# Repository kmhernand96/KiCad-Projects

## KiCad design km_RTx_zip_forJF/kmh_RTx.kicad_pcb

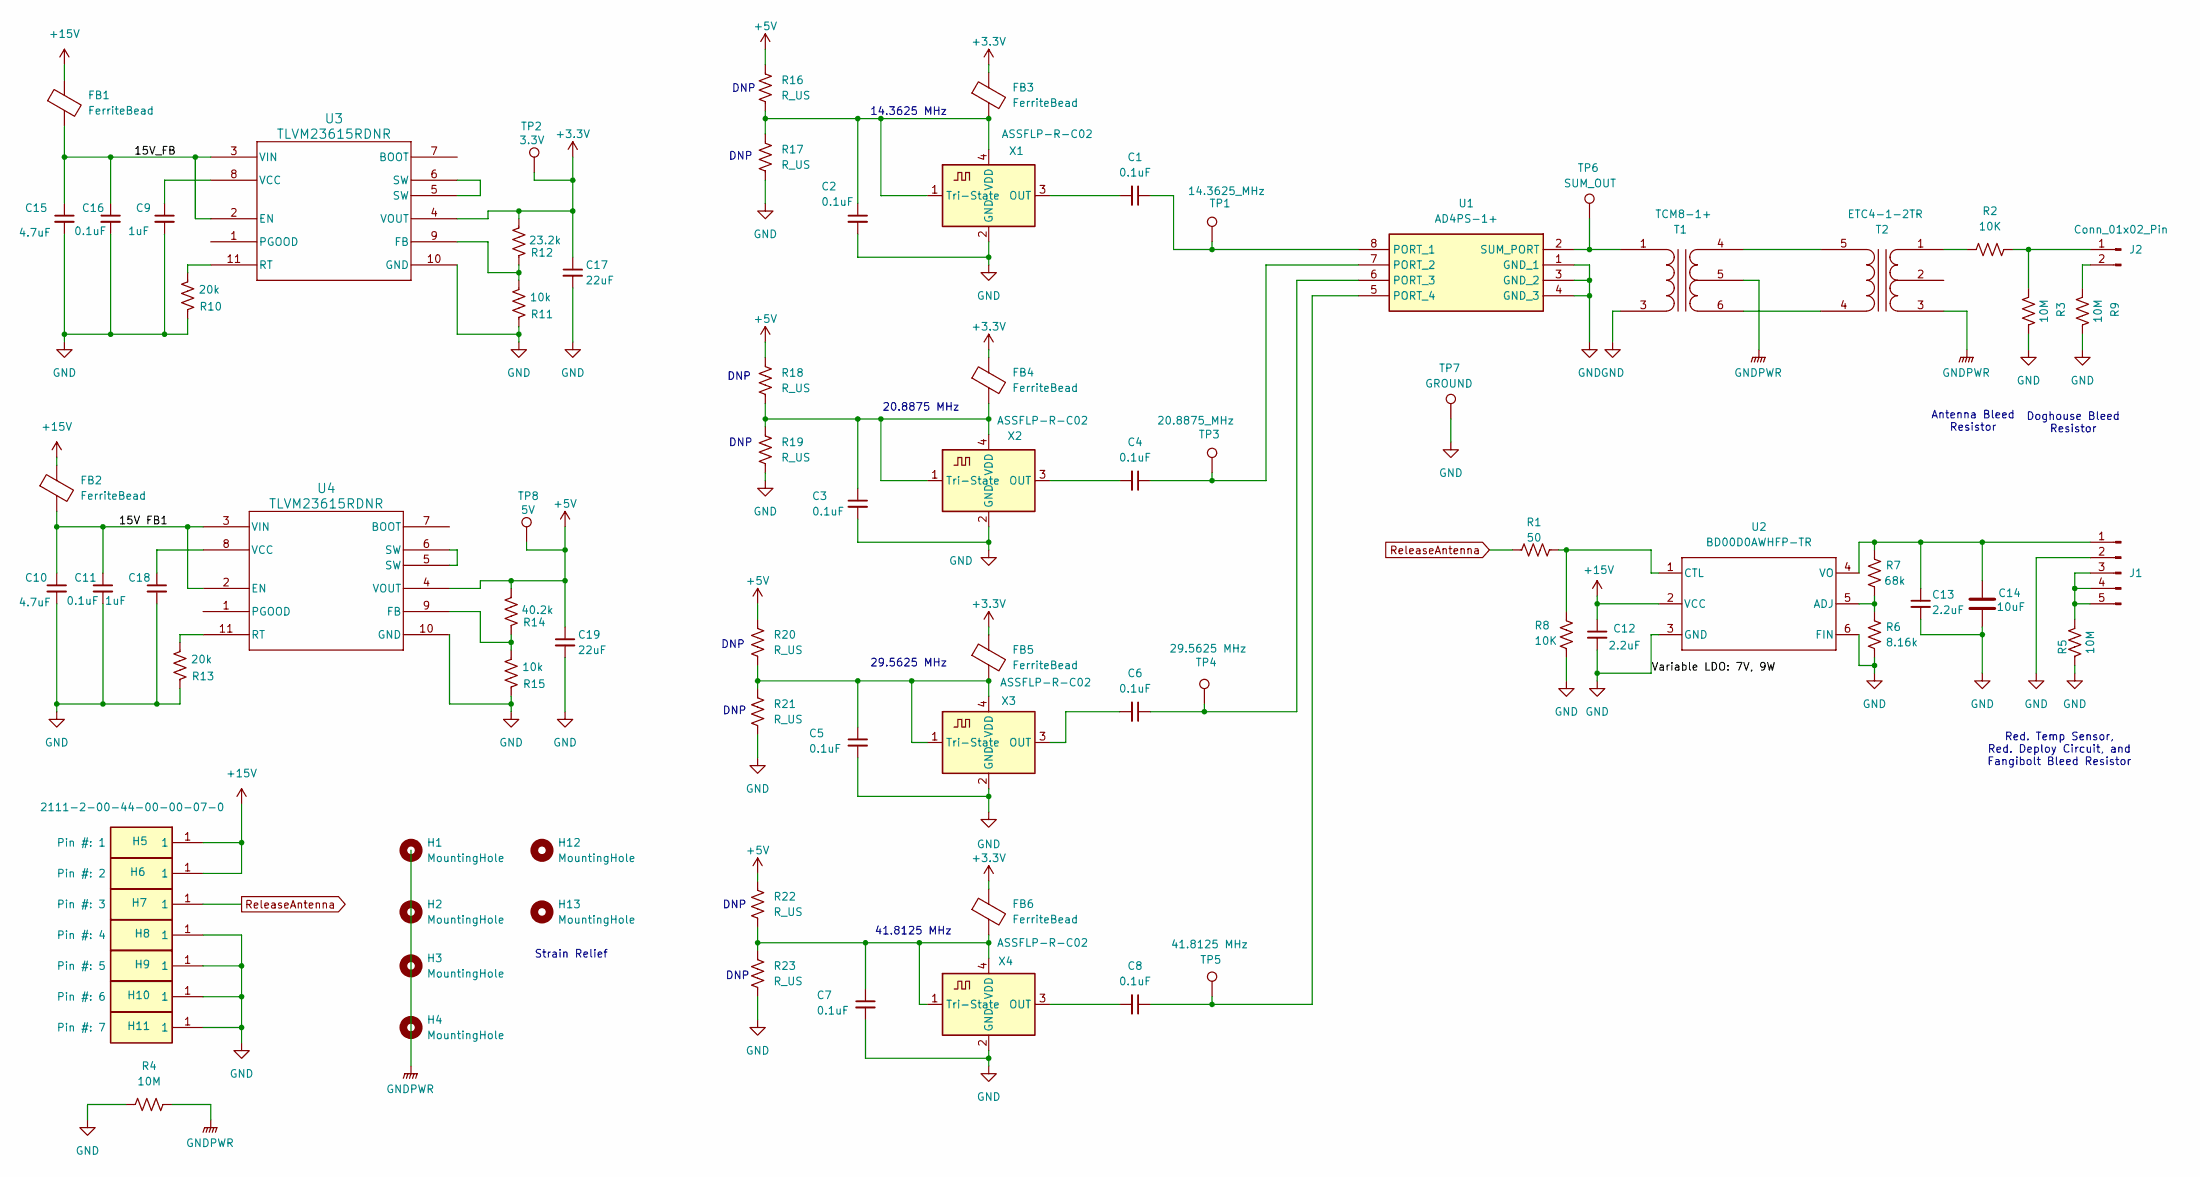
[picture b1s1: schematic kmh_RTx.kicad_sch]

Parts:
C1, C2, C3, C4, C5, C6, C7, C8, C11, C16: 0.1uF; C_0603_1608Metric
C9, C18: 1uF; C_0603_1608Metric
C10, C15: 4.7uF; C_1206_3216Metric
C12, C13: 2.2uF; C_1206_3216Metric
C14: 10uF; C_0805_2012Metric
C17, C19: 22uF; D_0805_2012Metric
FB1, FB2, FB3, FB4, FB5, FB6: FerriteBead; L_0805_2012Metric
H1, H2, H3, H4, H12, H13: MountingHole; MountingHole_2.5mm
H5, H6, H7, H8, H9, H10, H11: 2111-2-00-44-00-00-07-0; 2111200440000070; Mouser Part Number 575-2111200440000
J1: Conn_01x06_Pin; 22272051
J2: Conn_01x02_Pin; 22232021
R1: 50; R_0603_1608Metric
R2, R8: 10K; R_0603_1608Metric
R3, R4, R5, R9: 10M; R_0603_1608Metric
R6: 8.16k; R_0603_1608Metric
R7: 68k; R_0603_1608Metric
R10, R13: 20k; R_0603_1608Metric
R11, R15: 10k; R_0603_1608Metric
R12: 23.2k; R_0603_1608Metric
R14: 40.2k; R_0603_1608Metric
R16, R17, R18, R19, R20, R21, R22, R23: R_US; R_0603_1608Metric
T1: TCM8-1+; TCM81; Manufacturer_Part_Number TCM8-1+
T2: ETC4-1-2TR; ETC4_1_2TR; Manufacturer_Part_Number ETC4-1-2TR; Mouser Part Number 937-ETC4-1-2TR
TP1: 14.3625_MHz; 5000
TP2: 3.3V; Pin_D0.7mm_L6.5mm_W1.8mm_FlatFork
TP3: 20.8875_MHz; 5000
TP4: 29.5625 MHz; 5000
TP5: 41.8125 MHz; 5000
TP6: SUM_OUT; 5000
TP7: GROUND; 5000
TP8: 5V; Pin_D0.7mm_L6.5mm_W1.8mm_FlatFork
U1: AD4PS-1+; AD4PS1; Mouser Part Number 139-AD4PS-1
U2: BD00D0AWHFP-TR; HRP5_ROM; Manufacturer_Part_Number BD80FD0WHFP-TR; Mouser Part Number 755-BD80FD0WHFP-TR
U3, U4: TLVM23615RDNR; TLVM23615
X1, X2, X3, X4: ASSFLP-R-C02; Crystal_SMD_Abracon_ABM3B-4Pin_5.0x3.2mm

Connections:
+3.3V: C17.1, FB3.1, FB4.1, FB5.1, FB6.1, R12.2, TP2.1, U3.4 (VOUT)
+5V: C19.1, R14.2, R16.1, R18.1, R20.1, R22.1, TP8.1, U4.4 (VOUT)
+15V: C12.1, FB1.1, FB2.1, H5.1, H6.1, U2.2 (VCC)
/15V FB1: C10.1, C11.1, FB2.2, U4.2 (EN), U4.3 (VIN)
/15V_FB: C15.1, C16.1, FB1.2, U3.2 (EN), U3.3 (VIN)
GND: C2.2, C3.2, C5.2, C7.2, C9.2, C10.2, C11.2, C12.2, C13.2, C14.2, C15.2, C16.2, C17.2, C18.2, C19.2, H8.1, H9.1, H10.1, H11.1, J1.2, R3.1, R4.1, R5.1, R6.2, R8.2, R9.1, R10.1, R11.1, R13.1, R15.1, R17.2, R19.2, R21.2, R23.2, T1.3 (AB), TP7.1, U1.1 (GND_1), U1.3 (GND_2), U1.4 (GND_3), U2.3 (GND), U2.6 (FIN), U3.10 (GND), U4.10 (GND), X1.2 (GND), X2.2 (GND), X3.2 (GND), X4.2 (GND)
GNDPWR: R4.2, T1.5 (SC), T2.3 (SA)
unnamed: C13.1, C14.1, J1.1, R7.1, U2.4 (VO)
unnamed: J1.3, J1.4, J1.5, R5.2
unnamed: J2.1, R2.2, R3.2
unnamed: J2.2, R9.2
unnamed: T1.1 (AA), TP6.1, U1.2 (SUM_PORT)
unnamed: T1.6 (SA), T2.4 (AB)
unnamed: T1.4 (SB), T2.5 (AA)
unnamed: R2.1, T2.1 (SB)
unnamed: C1.1, TP1.1, U1.8 (PORT_1)
unnamed: C4.1, TP3.1, U1.7 (PORT_2)
unnamed: C6.1, TP4.1, U1.6 (PORT_3)
unnamed: C8.1, TP5.1, U1.5 (PORT_4)
unnamed: R6.1, R7.2, U2.5 (ADJ)
unnamed: R1.2, R8.1, U2.1 (CTL)
unnamed: R11.2, R12.1, U3.9 (FB)
unnamed: R10.2, U3.11 (RT)
unnamed: U3.5 (SW), U3.6 (SW)
unnamed: C9.1, U3.8 (VCC)
unnamed: R14.1, R15.2, U4.9 (FB)
unnamed: R13.2, U4.11 (RT)
unnamed: U4.5 (SW), U4.6 (SW)
unnamed: C18.1, U4.8 (VCC)
unnamed: C1.2, X1.3 (OUT)
unnamed: C2.1, FB3.2, R16.2, R17.1, X1.1 (Tri-State), X1.4 (VDD)
unnamed: C4.2, X2.3 (OUT)
unnamed: C3.1, FB4.2, R18.2, R19.1, X2.1 (Tri-State), X2.4 (VDD)
unnamed: C6.2, X3.3 (OUT)
unnamed: C5.1, FB5.2, R20.2, R21.1, X3.1 (Tri-State), X3.4 (VDD)
unnamed: C8.2, X4.3 (OUT)
unnamed: C7.1, FB6.2, R22.2, R23.1, X4.1 (Tri-State), X4.4 (VDD)
ReleaseAntenna: H7.1, R1.1

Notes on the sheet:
DNP
Doghouse Bleed Resistor
14.3625 MHz
20.8875 MHz
29.5625 MHz
Antenna Bleed Resistor
41.8125 MHz
Strain Relief
Red. Temp Sensor, Red. Deploy Circuit, and Fangibolt Bleed Resistor

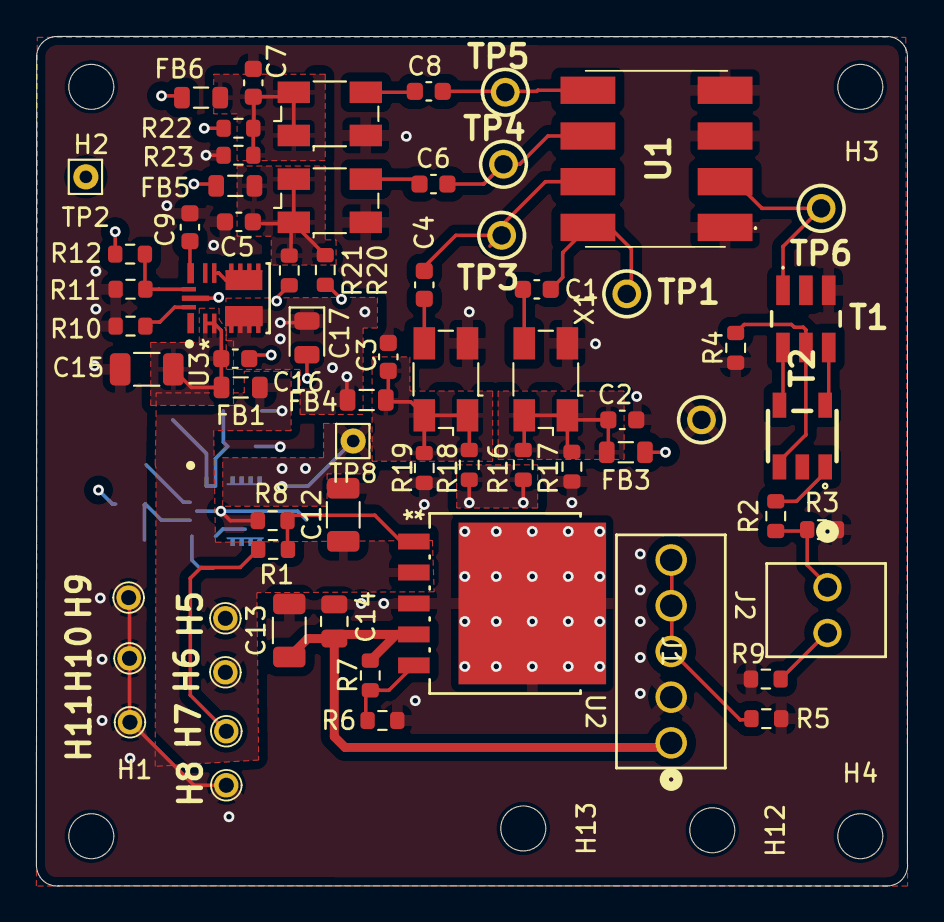
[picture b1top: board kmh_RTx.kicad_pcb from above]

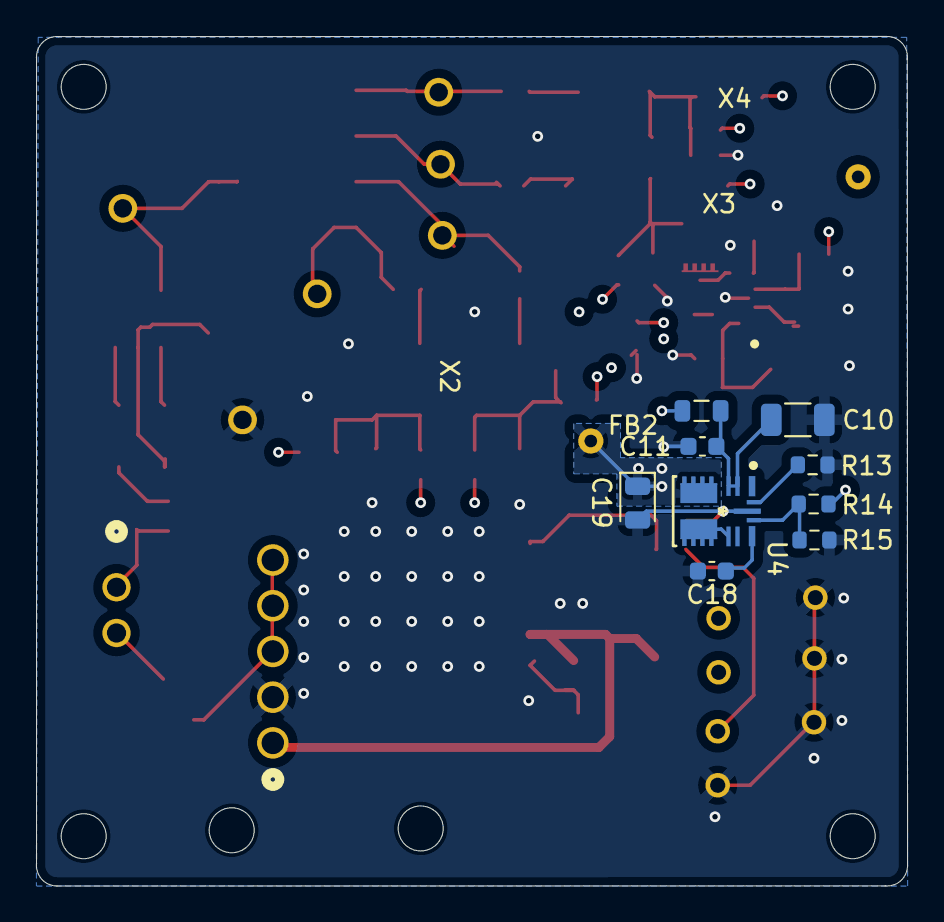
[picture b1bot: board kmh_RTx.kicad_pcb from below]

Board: 4 copper layers, 48.4 x 47.2 mm, 81 parts (9 on the bottom side), 38 nets.

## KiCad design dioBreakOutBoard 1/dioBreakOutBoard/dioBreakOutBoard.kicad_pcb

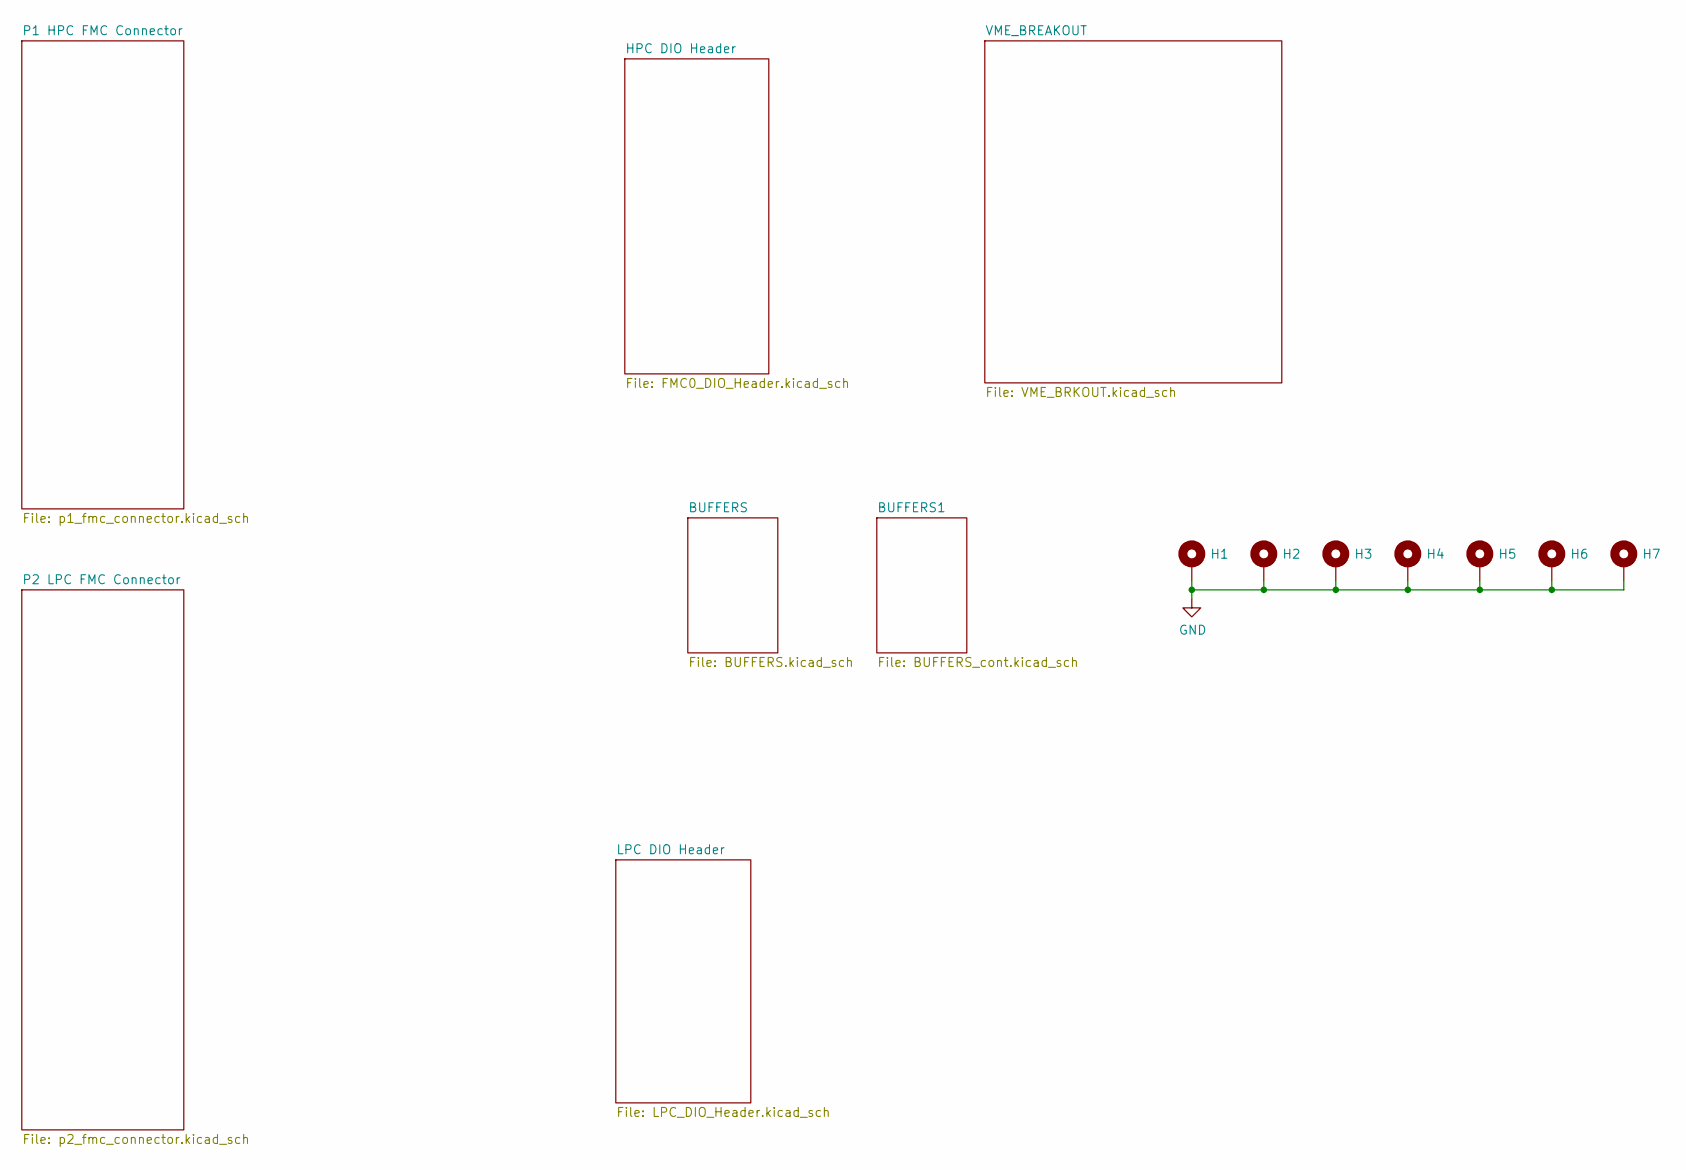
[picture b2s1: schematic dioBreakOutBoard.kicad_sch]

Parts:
H1, H2, H3, H4, H5, H6, H7: MountingHole_Pad; MountingHole_2.7mm_M2.5_ISO7380_Pad_TopBottom

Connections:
GND: H1.1, H2.1, H3.1, H4.1, H5.1, H6.1, H7.1; also elsewhere on the board

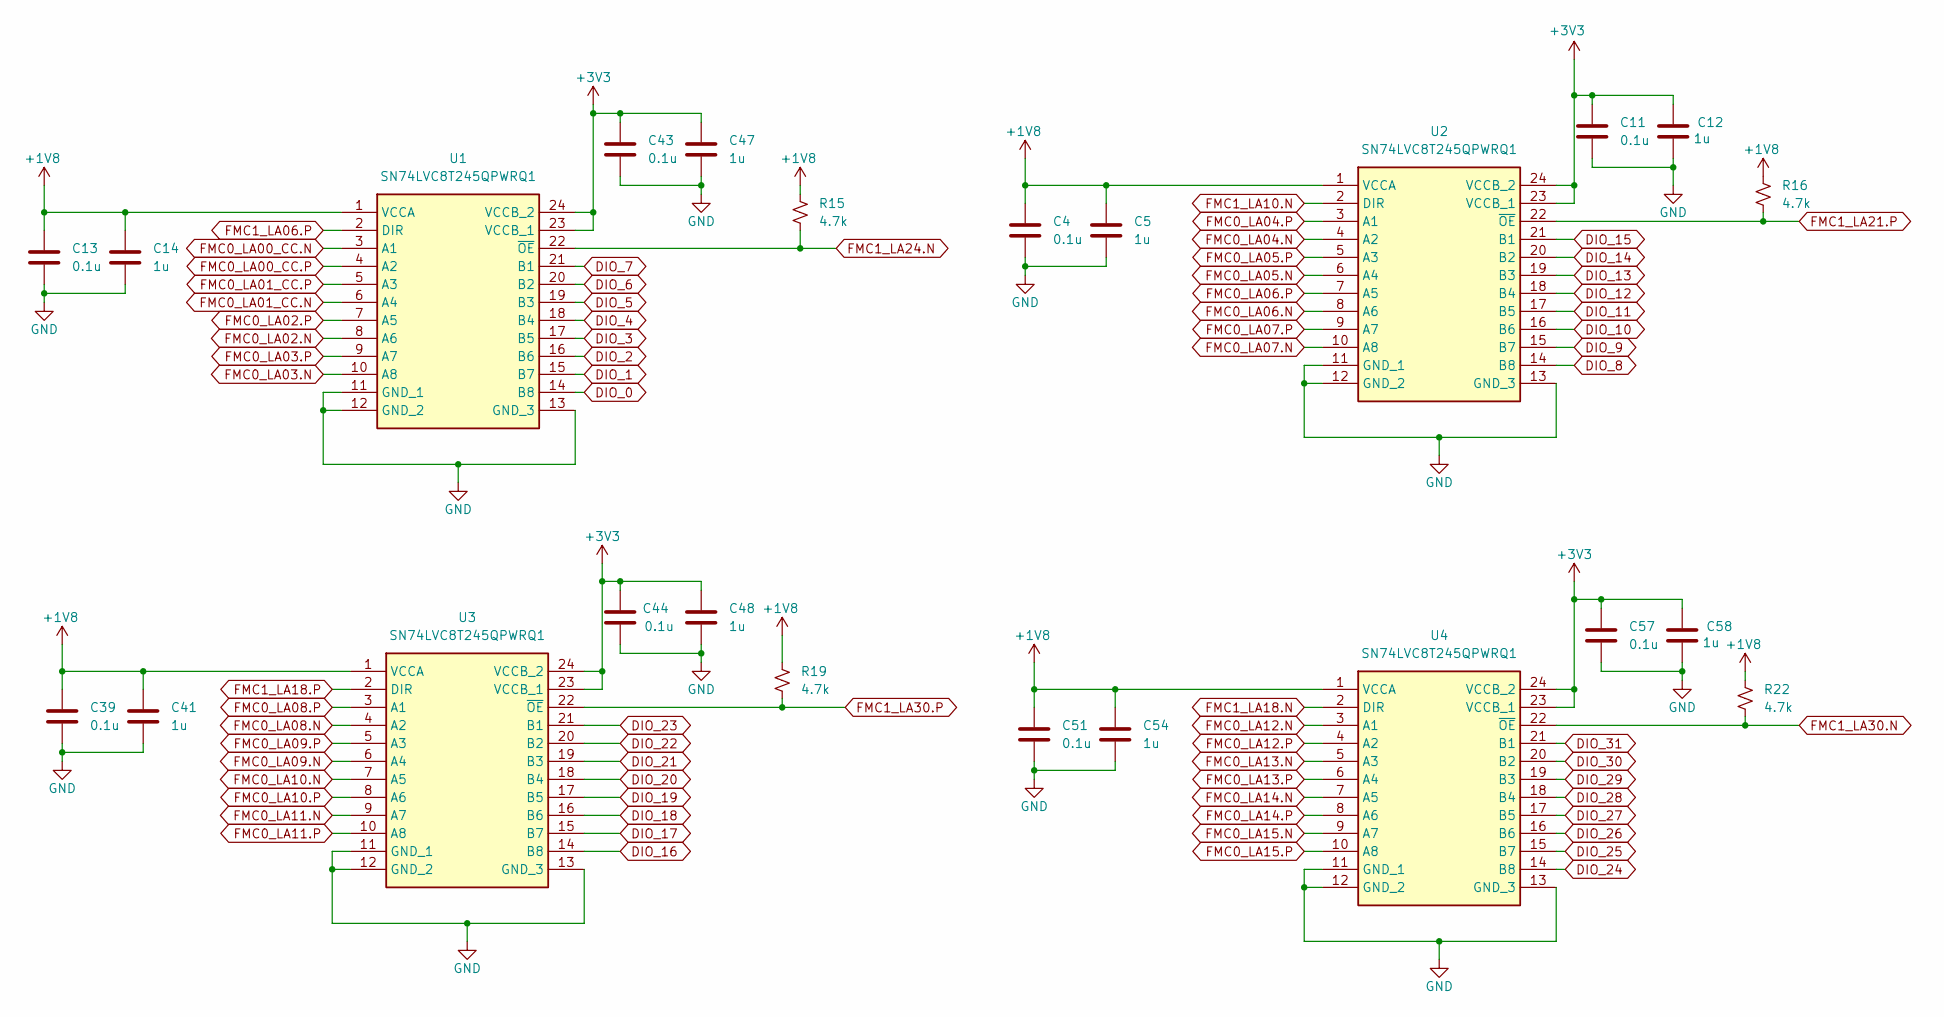
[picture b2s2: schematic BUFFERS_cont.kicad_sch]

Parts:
C4, C11, C13, C39, C43, C44, C51, C57: 0.1u; C_0603_1608Metric; MFG_PN TMK107BJ104KA-T
C5, C12, C14, C41, C47, C48, C54, C58: 1u; C_0805_2012Metric_Pad1.18x1.45mm_HandSolder; MFG_PN TMK212B7105KG-T
R15, R16, R19, R22: 4.7k; R_0603_1608Metric; MFG_PN CRCW06030000ZS
U1, U2, U3, U4: SN74LVC8T245QPWRQ1; SOP65P640X120-24N; Mouser Part Number 595-74LVC8T245QPWRQ1

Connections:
+1V8: C4.2, C5.2, C13.2, C14.2, C39.2, C41.2, C51.2, C54.2, R15.2, R16.2, R19.2, R22.2, U1.1 (VCCA), U2.1 (VCCA), U3.1 (VCCA), U4.1 (VCCA); also elsewhere on the board
+3V3: C11.2, C12.2, C43.2, C44.2, C47.2, C48.2, C57.2, C58.2, U1.23 (VCCB_1), U1.24 (VCCB_2), U2.23 (VCCB_1), U2.24 (VCCB_2), U3.23 (VCCB_1), U3.24 (VCCB_2), U4.23 (VCCB_1), U4.24 (VCCB_2); also elsewhere on the board
DIO_0: U1.14 (B8); also elsewhere on the board
DIO_1: U1.15 (B7); also elsewhere on the board
DIO_2: U1.16 (B6); also elsewhere on the board
DIO_3: U1.17 (B5); also elsewhere on the board
DIO_4: U1.18 (B4); also elsewhere on the board
DIO_5: U1.19 (B3); also elsewhere on the board
DIO_6: U1.20 (B2); also elsewhere on the board
DIO_7: U1.21 (B1); also elsewhere on the board
DIO_8: U2.14 (B8); also elsewhere on the board
DIO_9: U2.15 (B7); also elsewhere on the board
DIO_10: U2.16 (B6); also elsewhere on the board
DIO_11: U2.17 (B5); also elsewhere on the board
DIO_12: U2.18 (B4); also elsewhere on the board
DIO_13: U2.19 (B3); also elsewhere on the board
DIO_14: U2.20 (B2); also elsewhere on the board
DIO_15: U2.21 (B1); also elsewhere on the board
DIO_16: U3.14 (B8); also elsewhere on the board
DIO_17: U3.15 (B7); also elsewhere on the board
DIO_18: U3.16 (B6); also elsewhere on the board
DIO_19: U3.17 (B5); also elsewhere on the board
DIO_20: U3.18 (B4); also elsewhere on the board
DIO_21: U3.19 (B3); also elsewhere on the board
DIO_22: U3.20 (B2); also elsewhere on the board
DIO_23: U3.21 (B1); also elsewhere on the board
DIO_24: U4.14 (B8); also elsewhere on the board
DIO_25: U4.15 (B7); also elsewhere on the board
DIO_26: U4.16 (B6); also elsewhere on the board
DIO_27: U4.17 (B5); also elsewhere on the board
DIO_28: U4.18 (B4); also elsewhere on the board
DIO_29: U4.19 (B3); also elsewhere on the board
DIO_30: U4.20 (B2); also elsewhere on the board
DIO_31: U4.21 (B1); also elsewhere on the board
FMC0_LA00_CC.N: U1.3 (A1); also elsewhere on the board
FMC0_LA00_CC.P: U1.4 (A2); also elsewhere on the board
FMC0_LA01_CC.N: U1.6 (A4); also elsewhere on the board
FMC0_LA01_CC.P: U1.5 (A3); also elsewhere on the board
FMC0_LA02.N: U1.8 (A6); also elsewhere on the board
FMC0_LA02.P: U1.7 (A5); also elsewhere on the board
FMC0_LA03.N: U1.10 (A8); also elsewhere on the board
FMC0_LA03.P: U1.9 (A7); also elsewhere on the board
FMC0_LA04.N: U2.4 (A2); also elsewhere on the board
FMC0_LA04.P: U2.3 (A1); also elsewhere on the board
FMC0_LA05.N: U2.6 (A4); also elsewhere on the board
FMC0_LA05.P: U2.5 (A3); also elsewhere on the board
FMC0_LA06.N: U2.8 (A6); also elsewhere on the board
FMC0_LA06.P: U2.7 (A5); also elsewhere on the board
FMC0_LA07.N: U2.10 (A8); also elsewhere on the board
FMC0_LA07.P: U2.9 (A7); also elsewhere on the board
FMC0_LA08.N: U3.4 (A2); also elsewhere on the board
FMC0_LA08.P: U3.3 (A1); also elsewhere on the board
FMC0_LA09.N: U3.6 (A4); also elsewhere on the board
FMC0_LA09.P: U3.5 (A3); also elsewhere on the board
FMC0_LA10.N: U3.7 (A5); also elsewhere on the board
FMC0_LA10.P: U3.8 (A6); also elsewhere on the board
FMC0_LA11.N: U3.9 (A7); also elsewhere on the board
FMC0_LA11.P: U3.10 (A8); also elsewhere on the board
FMC0_LA12.N: U4.3 (A1); also elsewhere on the board
FMC0_LA12.P: U4.4 (A2); also elsewhere on the board
FMC0_LA13.N: U4.5 (A3); also elsewhere on the board
FMC0_LA13.P: U4.6 (A4); also elsewhere on the board
FMC0_LA14.N: U4.7 (A5); also elsewhere on the board
FMC0_LA14.P: U4.8 (A6); also elsewhere on the board
FMC0_LA15.N: U4.9 (A7); also elsewhere on the board
FMC0_LA15.P: U4.10 (A8); also elsewhere on the board
FMC1_LA06.P: U1.2 (DIR); also elsewhere on the board
FMC1_LA10.N: U2.2 (DIR); also elsewhere on the board
FMC1_LA18.N: U4.2 (DIR); also elsewhere on the board
FMC1_LA18.P: U3.2 (DIR); also elsewhere on the board
FMC1_LA21.P: R16.1, U2.22 (~OE); also elsewhere on the board
FMC1_LA24.N: R15.1, U1.22 (~OE); also elsewhere on the board
FMC1_LA30.N: R22.1, U4.22 (~OE); also elsewhere on the board
FMC1_LA30.P: R19.1, U3.22 (~OE); also elsewhere on the board
GND: C4.1, C5.1, C11.1, C12.1, C13.1, C14.1, C39.1, C41.1, C43.1, C44.1, C47.1, C48.1, C51.1, C54.1, C57.1, C58.1, U1.11 (GND_1), U1.12 (GND_2), U1.13 (GND_3), U2.11 (GND_1), U2.12 (GND_2), U2.13 (GND_3), U3.11 (GND_1), U3.12 (GND_2), U3.13 (GND_3), U4.11 (GND_1), U4.12 (GND_2), U4.13 (GND_3); also elsewhere on the board

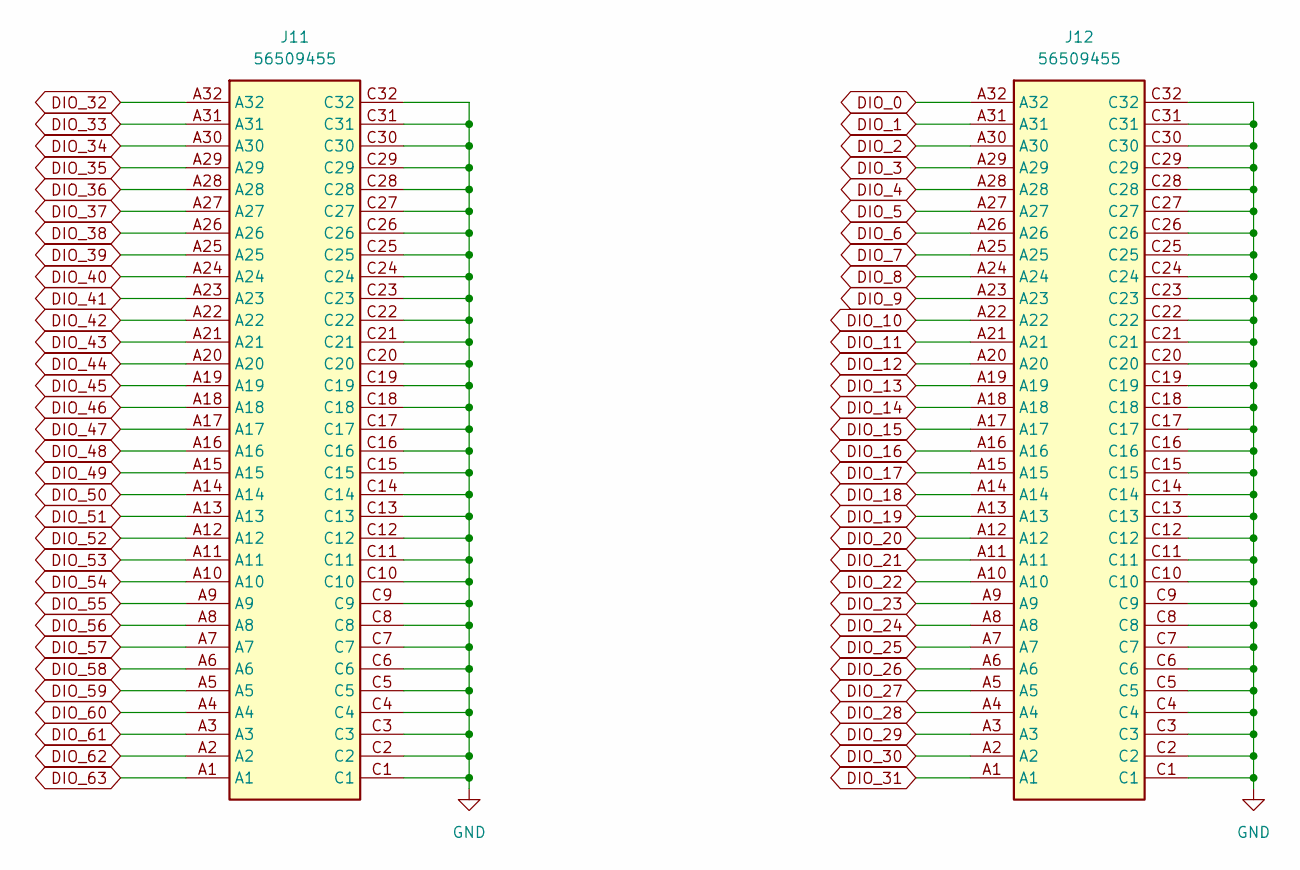
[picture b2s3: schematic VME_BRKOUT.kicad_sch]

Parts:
J11, J12: 56509455; Mouser Part Number 617-09-03-164-6922

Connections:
DIO_0: J12.A32; also elsewhere on the board
DIO_1: J12.A31; also elsewhere on the board
DIO_2: J12.A30; also elsewhere on the board
DIO_3: J12.A29; also elsewhere on the board
DIO_4: J12.A28; also elsewhere on the board
DIO_5: J12.A27; also elsewhere on the board
DIO_6: J12.A26; also elsewhere on the board
DIO_7: J12.A25; also elsewhere on the board
DIO_8: J12.A24; also elsewhere on the board
DIO_9: J12.A23; also elsewhere on the board
DIO_10: J12.A22; also elsewhere on the board
DIO_11: J12.A21; also elsewhere on the board
DIO_12: J12.A20; also elsewhere on the board
DIO_13: J12.A19; also elsewhere on the board
DIO_14: J12.A18; also elsewhere on the board
DIO_15: J12.A17; also elsewhere on the board
DIO_16: J12.A16; also elsewhere on the board
DIO_17: J12.A15; also elsewhere on the board
DIO_18: J12.A14; also elsewhere on the board
DIO_19: J12.A13; also elsewhere on the board
DIO_20: J12.A12; also elsewhere on the board
DIO_21: J12.A11; also elsewhere on the board
DIO_22: J12.A10; also elsewhere on the board
DIO_23: J12.A9; also elsewhere on the board
DIO_24: J12.A8; also elsewhere on the board
DIO_25: J12.A7; also elsewhere on the board
DIO_26: J12.A6; also elsewhere on the board
DIO_27: J12.A5; also elsewhere on the board
DIO_28: J12.A4; also elsewhere on the board
DIO_29: J12.A3; also elsewhere on the board
DIO_30: J12.A2; also elsewhere on the board
DIO_31: J12.A1; also elsewhere on the board
DIO_32: J11.A32; also elsewhere on the board
DIO_33: J11.A31; also elsewhere on the board
DIO_34: J11.A30; also elsewhere on the board
DIO_35: J11.A29; also elsewhere on the board
DIO_36: J11.A28; also elsewhere on the board
DIO_37: J11.A27; also elsewhere on the board
DIO_38: J11.A26; also elsewhere on the board
DIO_39: J11.A25; also elsewhere on the board
DIO_40: J11.A24; also elsewhere on the board
DIO_41: J11.A23; also elsewhere on the board
DIO_42: J11.A22; also elsewhere on the board
DIO_43: J11.A21; also elsewhere on the board
DIO_44: J11.A20; also elsewhere on the board
DIO_45: J11.A19; also elsewhere on the board
DIO_46: J11.A18; also elsewhere on the board
DIO_47: J11.A17; also elsewhere on the board
DIO_48: J11.A16; also elsewhere on the board
DIO_49: J11.A15; also elsewhere on the board
DIO_50: J11.A14; also elsewhere on the board
DIO_51: J11.A13; also elsewhere on the board
DIO_52: J11.A12; also elsewhere on the board
DIO_53: J11.A11; also elsewhere on the board
DIO_54: J11.A10; also elsewhere on the board
DIO_55: J11.A9; also elsewhere on the board
DIO_56: J11.A8; also elsewhere on the board
DIO_57: J11.A7; also elsewhere on the board
DIO_58: J11.A6; also elsewhere on the board
DIO_59: J11.A5; also elsewhere on the board
DIO_60: J11.A4; also elsewhere on the board
DIO_61: J11.A3; also elsewhere on the board
DIO_62: J11.A2; also elsewhere on the board
DIO_63: J11.A1; also elsewhere on the board
GND: J11.C1, J11.C2, J11.C3, J11.C4, J11.C5, J11.C6, J11.C7, J11.C8, J11.C9, J11.C10, J11.C11, J11.C12, J11.C13, J11.C14, J11.C15, J11.C16, J11.C17, J11.C18, J11.C19, J11.C20, J11.C21, J11.C22, J11.C23, J11.C24, J11.C25, J11.C26, J11.C27, J11.C28, J11.C29, J11.C30, J11.C31, J11.C32, J12.C1, J12.C2, J12.C3, J12.C4, J12.C5, J12.C6, J12.C7, J12.C8, J12.C9, J12.C10, J12.C11, J12.C12, J12.C13, J12.C14, J12.C15, J12.C16, J12.C17, J12.C18, J12.C19, J12.C20, J12.C21, J12.C22, J12.C23, J12.C24, J12.C25, J12.C26, J12.C27, J12.C28, J12.C29, J12.C30, J12.C31, J12.C32; also elsewhere on the board

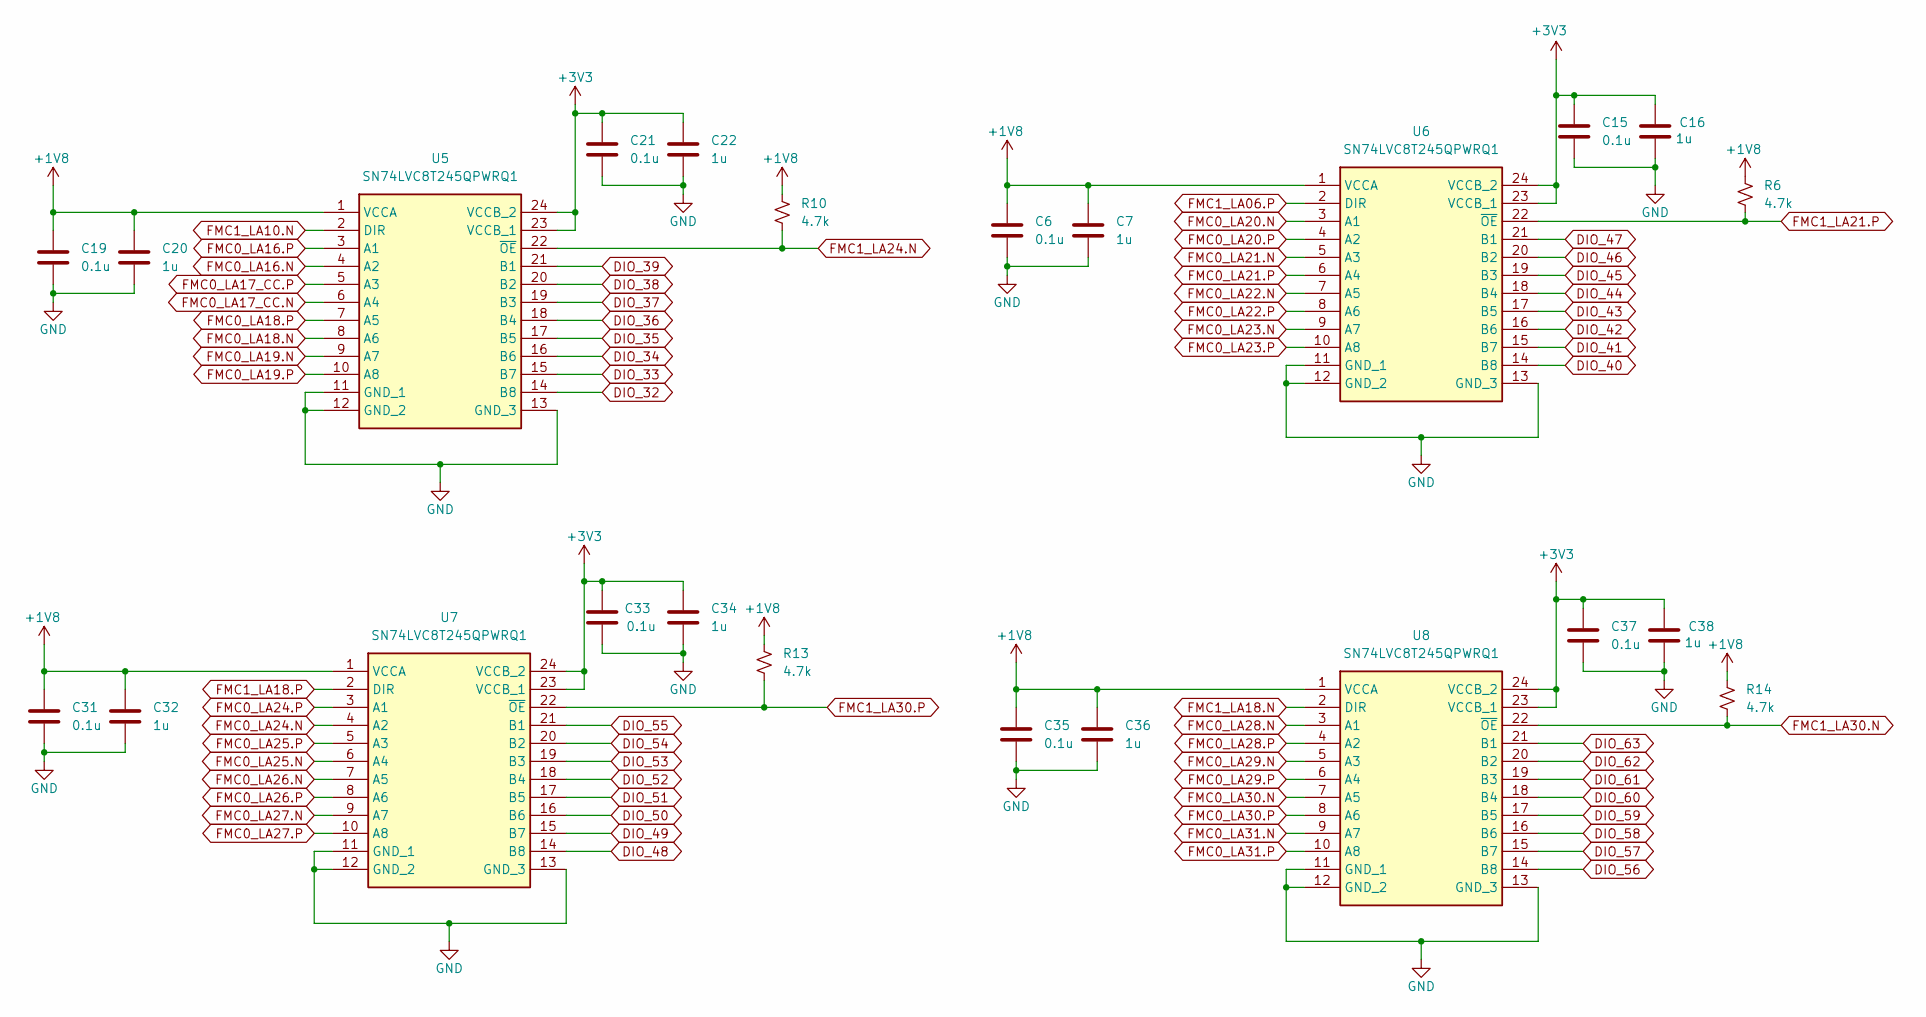
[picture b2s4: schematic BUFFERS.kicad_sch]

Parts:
C6, C15, C19, C21, C31, C33, C35, C37: 0.1u; C_0603_1608Metric; MFG_PN TMK107BJ104KA-T
C7, C16, C20, C22, C32, C34, C36, C38: 1u; C_0805_2012Metric_Pad1.18x1.45mm_HandSolder; MFG_PN TMK212B7105KG-T
R6, R10, R13, R14: 4.7k; R_0603_1608Metric; MFG_PN CRCW06030000ZS
U5, U6, U7, U8: SN74LVC8T245QPWRQ1; SOP65P640X120-24N; Mouser Part Number 595-74LVC8T245QPWRQ1

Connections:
+1V8: C6.2, C7.2, C19.2, C20.2, C31.2, C32.2, C35.2, C36.2, R6.2, R10.2, R13.2, R14.2, U5.1 (VCCA), U6.1 (VCCA), U7.1 (VCCA), U8.1 (VCCA); also elsewhere on the board
+3V3: C15.2, C16.2, C21.2, C22.2, C33.2, C34.2, C37.2, C38.2, U5.23 (VCCB_1), U5.24 (VCCB_2), U6.23 (VCCB_1), U6.24 (VCCB_2), U7.23 (VCCB_1), U7.24 (VCCB_2), U8.23 (VCCB_1), U8.24 (VCCB_2); also elsewhere on the board
DIO_32: U5.14 (B8); also elsewhere on the board
DIO_33: U5.15 (B7); also elsewhere on the board
DIO_34: U5.16 (B6); also elsewhere on the board
DIO_35: U5.17 (B5); also elsewhere on the board
DIO_36: U5.18 (B4); also elsewhere on the board
DIO_37: U5.19 (B3); also elsewhere on the board
DIO_38: U5.20 (B2); also elsewhere on the board
DIO_39: U5.21 (B1); also elsewhere on the board
DIO_40: U6.14 (B8); also elsewhere on the board
DIO_41: U6.15 (B7); also elsewhere on the board
DIO_42: U6.16 (B6); also elsewhere on the board
DIO_43: U6.17 (B5); also elsewhere on the board
DIO_44: U6.18 (B4); also elsewhere on the board
DIO_45: U6.19 (B3); also elsewhere on the board
DIO_46: U6.20 (B2); also elsewhere on the board
DIO_47: U6.21 (B1); also elsewhere on the board
DIO_48: U7.14 (B8); also elsewhere on the board
DIO_49: U7.15 (B7); also elsewhere on the board
DIO_50: U7.16 (B6); also elsewhere on the board
DIO_51: U7.17 (B5); also elsewhere on the board
DIO_52: U7.18 (B4); also elsewhere on the board
DIO_53: U7.19 (B3); also elsewhere on the board
DIO_54: U7.20 (B2); also elsewhere on the board
DIO_55: U7.21 (B1); also elsewhere on the board
DIO_56: U8.14 (B8); also elsewhere on the board
DIO_57: U8.15 (B7); also elsewhere on the board
DIO_58: U8.16 (B6); also elsewhere on the board
DIO_59: U8.17 (B5); also elsewhere on the board
DIO_60: U8.18 (B4); also elsewhere on the board
DIO_61: U8.19 (B3); also elsewhere on the board
DIO_62: U8.20 (B2); also elsewhere on the board
DIO_63: U8.21 (B1); also elsewhere on the board
FMC0_LA16.N: U5.4 (A2); also elsewhere on the board
FMC0_LA16.P: U5.3 (A1); also elsewhere on the board
FMC0_LA17_CC.N: U5.6 (A4); also elsewhere on the board
FMC0_LA17_CC.P: U5.5 (A3); also elsewhere on the board
FMC0_LA18.N: U5.8 (A6); also elsewhere on the board
FMC0_LA18.P: U5.7 (A5); also elsewhere on the board
FMC0_LA19.N: U5.9 (A7); also elsewhere on the board
FMC0_LA19.P: U5.10 (A8); also elsewhere on the board
FMC0_LA20.N: U6.3 (A1); also elsewhere on the board
FMC0_LA20.P: U6.4 (A2); also elsewhere on the board
FMC0_LA21.N: U6.5 (A3); also elsewhere on the board
FMC0_LA21.P: U6.6 (A4); also elsewhere on the board
FMC0_LA22.N: U6.7 (A5); also elsewhere on the board
FMC0_LA22.P: U6.8 (A6); also elsewhere on the board
FMC0_LA23.N: U6.9 (A7); also elsewhere on the board
FMC0_LA23.P: U6.10 (A8); also elsewhere on the board
FMC0_LA24.N: U7.4 (A2); also elsewhere on the board
FMC0_LA24.P: U7.3 (A1); also elsewhere on the board
FMC0_LA25.N: U7.6 (A4); also elsewhere on the board
FMC0_LA25.P: U7.5 (A3); also elsewhere on the board
FMC0_LA26.N: U7.7 (A5); also elsewhere on the board
FMC0_LA26.P: U7.8 (A6); also elsewhere on the board
FMC0_LA27.N: U7.9 (A7); also elsewhere on the board
FMC0_LA27.P: U7.10 (A8); also elsewhere on the board
FMC0_LA28.N: U8.3 (A1); also elsewhere on the board
FMC0_LA28.P: U8.4 (A2); also elsewhere on the board
FMC0_LA29.N: U8.5 (A3); also elsewhere on the board
FMC0_LA29.P: U8.6 (A4); also elsewhere on the board
FMC0_LA30.N: U8.7 (A5); also elsewhere on the board
FMC0_LA30.P: U8.8 (A6); also elsewhere on the board
FMC0_LA31.N: U8.9 (A7); also elsewhere on the board
FMC0_LA31.P: U8.10 (A8); also elsewhere on the board
FMC1_LA06.P: U6.2 (DIR); also elsewhere on the board
FMC1_LA10.N: U5.2 (DIR); also elsewhere on the board
FMC1_LA18.N: U8.2 (DIR); also elsewhere on the board
FMC1_LA18.P: U7.2 (DIR); also elsewhere on the board
FMC1_LA21.P: R6.1, U6.22 (~OE); also elsewhere on the board
FMC1_LA24.N: R10.1, U5.22 (~OE); also elsewhere on the board
FMC1_LA30.N: R14.1, U8.22 (~OE); also elsewhere on the board
FMC1_LA30.P: R13.1, U7.22 (~OE); also elsewhere on the board
GND: C6.1, C7.1, C15.1, C16.1, C19.1, C20.1, C21.1, C22.1, C31.1, C32.1, C33.1, C34.1, C35.1, C36.1, C37.1, C38.1, U5.11 (GND_1), U5.12 (GND_2), U5.13 (GND_3), U6.11 (GND_1), U6.12 (GND_2), U6.13 (GND_3), U7.11 (GND_1), U7.12 (GND_2), U7.13 (GND_3), U8.11 (GND_1), U8.12 (GND_2), U8.13 (GND_3); also elsewhere on the board
